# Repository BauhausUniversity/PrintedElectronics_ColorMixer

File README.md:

# PrintedElectronics_ColorMixer
A simple printed electronics interface to an analog RGB LED using velostat.

This [layout](layout.pdf) can be printed using silver ink or laser cut as a stencil and then drawn by hand through the stencil with conductive pens.

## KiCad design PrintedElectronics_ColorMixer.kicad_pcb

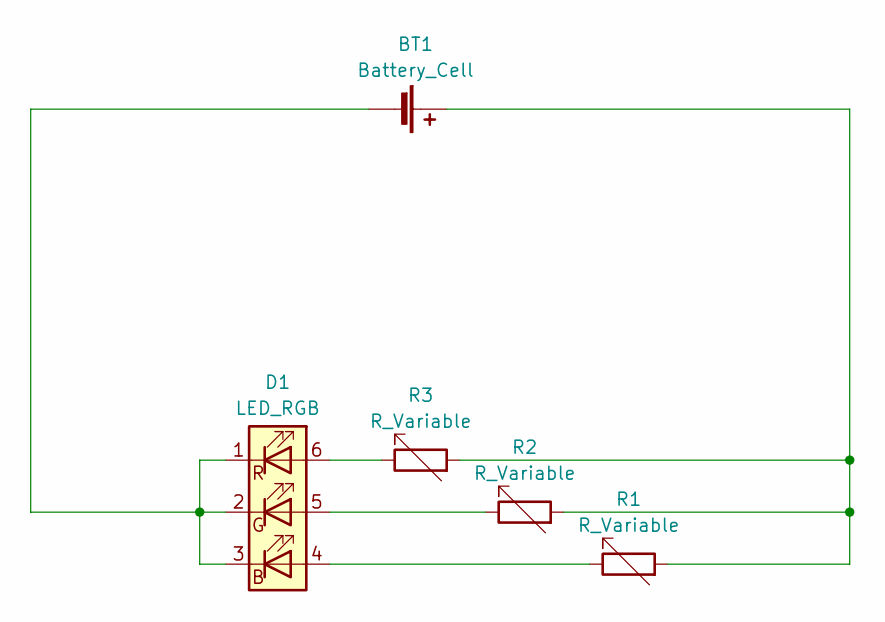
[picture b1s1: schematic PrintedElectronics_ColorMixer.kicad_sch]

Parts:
BT1: Battery_Cell; BatteryHolder_2032_Printed_Electronics
D1: LED_RGB; LED_RGB_5050-6
R1, R2, R3: R_Variable; Humidity_Sensor_Printed_Electronics_Stencil

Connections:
unnamed: BT1.1 (+), R1.2, R2.2, R3.2
unnamed: BT1.2 (-), D1.1 (RK), D1.2 (GK), D1.3 (BK)
unnamed: D1.4 (BA), R1.1
unnamed: D1.5 (GA), R2.1
unnamed: D1.6 (RA), R3.1

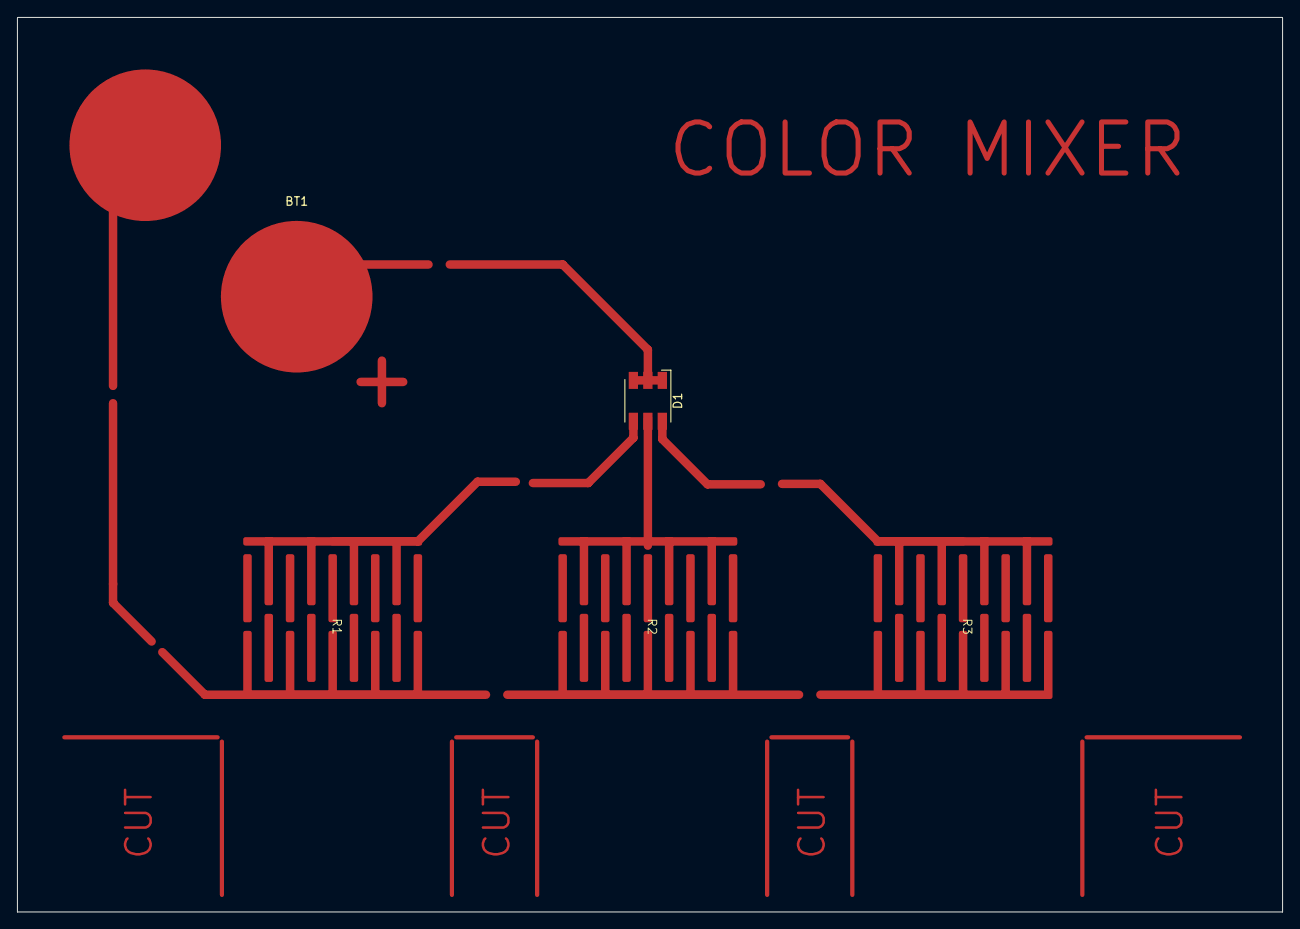
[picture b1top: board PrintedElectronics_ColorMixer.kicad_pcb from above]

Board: 2 copper layers, 148.5 x 105.0 mm, 5 parts (0 on the bottom side), 5 nets.

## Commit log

2023-11-26 initial schematic and layout
2023-11-27 coarser humditiy sensor and bridges for stencils
